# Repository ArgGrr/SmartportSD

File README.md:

# SmartportSD
Fork of SmartportSD by Andrea Ottaviani which is a port of Apple //c Smartport Compact Flash adpater by Robert Justice.
Original source: http://www.users.on.net/~rjustice/SmartportCFA/SmartportSD.htm
Added here for convenience, not intending to take over the project!

I have added some code to support a small OLED display to show some information, rework the code a little for better or worse.

Includes a 3d printable DB15 plug housing for the smartport. You will need some real pins.

Also includes a work in progress case that somewhat looks like a 3.5 inch unidisk drive, from pictures anyway.

To build you'll need to install the U8g2 library from Arduino Library Manager.
I am using the following screen: Geekcreit 0.91 Inch 128x32 IIC I2C Blue OLED Display DIY Oled Module SSD1306 Driver.

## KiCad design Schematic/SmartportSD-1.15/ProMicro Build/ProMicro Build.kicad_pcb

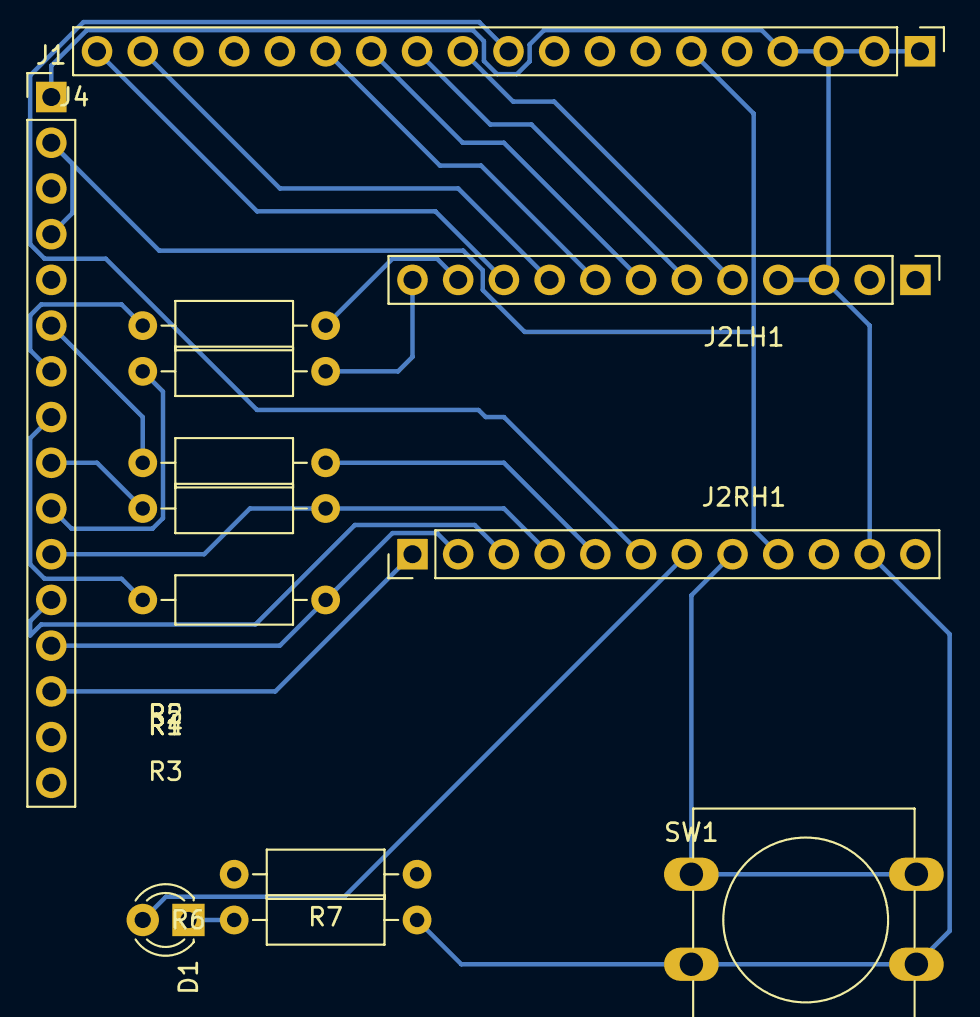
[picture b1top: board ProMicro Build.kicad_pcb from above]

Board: 2 copper layers, 13 parts (0 on the bottom side), 24 nets.

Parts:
D1: LED; LED_D3.0mm
J1: QDtech_1.8inch_SPI_MSP1804; PinHeader_1x16_P2.54mm_Vertical
J2LH1, J2RH1: Conn_01x12; PinHeader_1x12_P2.54mm_Vertical
J4: Apple 2 Drive Port; PinHeader_1x19_P2.54mm_Vertical
R1, R2, R3, R4, R5: 2k2; R_Axial_DIN0207_L6.3mm_D2.5mm_P10.16mm_Horizontal
R6: 100R; R_Axial_DIN0207_L6.3mm_D2.5mm_P10.16mm_Horizontal
R7: 10k; R_Axial_DIN0207_L6.3mm_D2.5mm_P10.16mm_Horizontal
SW1: SW_Push; SW_PUSH-12mm

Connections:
+5V: J1.2, J1.4, J2RH1.9, J4.6, R7.2
CLK: J1.11, J2RH1.4, R4.2
EJECT_PIN: J2RH1.8, R7.1, SW1.1
GND: J1.1, J2LH1.3, J2LH1.4, J2RH1.11, J4.1, J4.2, J4.3, J4.4, R6.2, SW1.2
MISO: J1.12, J2RH1.3
MOSI: J1.13, J2RH1.2, R3.2
unnamed: D1.1, R6.1
unnamed: J1.6, R1.1
unnamed: J1.7, R2.1
unnamed: J1.8, R3.1
unnamed: J1.9, R4.1
unnamed: J1.10, R5.1
RDDATA: J2LH1.9, J4.18
SD_CS: J1.14, J2RH1.1
SEEKPH0: J2LH1.5, J4.11
SEEKPH1: J2LH1.6, J4.12
SEEKPH2: J2LH1.7, J4.13
SEEKPH3: J2LH1.8, J4.14
STATUS_LED: D1.2, J2RH1.7
TFT_CS: J2LH1.12, R5.2
TFT_DC: J2LH1.11, R2.2
TFT_RESET: J2RH1.5, R1.2
WRDATA: J2LH1.10, J4.19
WRPROT: J2RH1.6, J4.10

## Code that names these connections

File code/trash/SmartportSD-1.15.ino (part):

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//
// Apple disk interface is connected as follows:
/*                                        | Pro Micro
 * wrprot = pa5 (ack) (output)            | A1 PF6
 * ph0    = pd2 (req) (input)             | D2 PD1
 * ph1    = pd3       (input)             | D3 PD0
 * ph2    = pd4       (input)             | D4 PD4
 * ph3    = pd5       (input)             | D5 PC6
 * rddata = pd6       (output from avr)   | D6 PD7
 * wrdata = pd7       (input to avr)      | D7 PE6
 *
 * _SFR_IO_ADDR(PORTC),5  ACK             | _SFR_IO_ADDR(PORTF),6 
 * _SFR_IO_ADDR(PIND), 2  REQ             | _SFR_IO_ADDR(PIND),1 
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 *          GND    ║    ║    VCC
 * PH0      SDA  2 ║    ║ 21 A3     EJECT PIN
 * PH1      SCL  3 ║    ║ 20 A2     STATUS LED
 * PH2      A6   4 ║    ║ 19 A1     WRPROT
 * PH3           5 ║    ║ 18 A0     TFT RST
 * RDATA    A7   6 ║    ║ 15 SCLK   SPICLK
 * WDATA         7 ║    ║ 14 MISO   SPIMISO
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// ** MOSI - pin 16 Arduino Pro Micro
// ** MISO - pin 14 Arduino Pro Micro
// ** CLK  - pin 15 Arduino Pro Micro
const uint8_t SD_CS = 10;

const uint8_t TFT_CS = 9;
const uint8_t TFT_DC = 8;
const uint8_t TFT_RST = A0;

// Misc drive I/O
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  pinMode(pinEject, INPUT);
  pinMode(pinStatusLED, OUTPUT);

  //pinMode(TFT_CS,OUTPUT);
  //pinMode(TFT_DC,OUTPUT);
  //pinMode(TFT_RST,OUTPUT);
}

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
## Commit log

2021-01-03 Arduino Pro-Micro, LCD & SD rework
    Reworked v1.15 project for Arduino Pro-Micro.
    Added support for combined LCD & SD card module.
    Code tidy up, organise etc.
2021-01-03 Folder Cleanup
